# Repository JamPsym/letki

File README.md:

# Letki modular LED display

Letki is a low-cost chain of 8×8 LED tiles with PWM brightness, programmable
text/graphics and synchronized music shows. The current physical baseline is
five v3 boards running the UART-programmable **general firmware R3**. The
independently developed v3.2 hardware and ESP8266/X035 attachment are the next
workstreams; their preparation and qualification status are recorded separately.

## Start here

- [Documentation index](docs/README.md): architecture, firmware, hardware and tests.
- [Current project state](docs/current-state.md): accepted revisions, orders,
  assembly substitutions and next work; later dated entries supersede older ones.
- [R3 milestone](docs/milestones/v3-general-r3-20261017.txt): verified five-board
  firmware, recovery references and physical validation limits.
- [Contributor instructions](AGENTS.md): working rules and hardware permissions.
- [Toolchain setup](docs/arch-setup.md): compiler and host dependencies.

## Desktop app and music

[Letki Studio](host/control/README.md) is a native GTK4/libadwaita application.
It provides text/font controls, brightness modulation, a five-tile pixel canvas,
presets, diagnostics and demos. The `letkid` service owns UART; Studio, the CLI
and other applications share its [local API](host/control/API.md).

```sh
make control-run
```

Drafts stay local until Apply. Applied RAM content runs independently of the GUI;
power cycling restores the saved flash show. Content uploads do not reflash the
application. Close picocom before connecting the service.

The [native C++ player](host/player/README.txt) uses the audio playback clock for
video and LED timing. Studio's Demo tab lists all [five music/video shows](docs/music-demos.md),
including the Laskowski × 2Pac mashup. Video plays on the PC beside the simulator.

```sh
make player
build/player/letki-player --show config/player/my-cyganie-full.json --simulate
make demos-prepare
```

`--simulate` forces PC-only playback. The direct player otherwise discovers a
WCH-Link UART adapter; release the broker's UART connection before using it.
`make demos-prepare` validates and renders local media offline without opening
UART or playing audio. Recordings are optional local data, not included in Git.

## Firmware and checks

The default build retains the original single-board text v3 application. Build
the current five-board general firmware with `make general-images`.

```sh
make doctor
make -j4
make general-images -j4
make test
make all-variants -j4
make player-test
make control-test
```

Builds never program a board. Physical tests and firmware writes follow the
identification, backup, readback and permission rules in [AGENTS.md](AGENTS.md).
Host register mocks and simulations do not establish electrical qualification.

## Layout

| Directory | Contents |
| --- | --- |
| `firmware/` | Maintained applications and separate diagnostic/demo variants |
| `host/` | Native Studio/service, music player and firmware renderers |
| `hw/` | Active KiCad projects, local libraries and mechanical sources |
| `config/` | Project settings, show cue sheets and selected purchase records |
| `scripts/` | Build/setup helpers, host controls and scoped CAD tools |
| `tests/` | Firmware register mocks and host/integration checks |
| `docs/` | Current decisions, architecture, validation and dated history |
| `archive/` | Superseded firmware, hardware and purchase drafts |
| `build/` | Ignored binaries, raw test evidence, media and working experiments |

See [hardware projects](hw/README.md) before opening a board. Existing v3 boards
require the documented C1–C3 ground repair. CAD and manufacturing exports have
their own qualification status; a successful software build is not a fabrication
release. Historical variants retain their notices and remain buildable.

## Development context and local data

The [attachment architecture](docs/attachments-study-20261017.txt) keeps tile
protocols independent of the host: ESP8266 → SPI → X035 → display. The media/TV
host is the **last planned system component**, with the spare N5095/M2S as a
candidate; development can continue after its integration.

Project decisions and source belong in Git. Generated binaries, recordings,
readbacks, caches, CAD editor state and fabrication exports remain local.
Shared electronics inventory is maintained outside this repository; see
[configuration setup](config/README.md) before using procurement generators.
These local datasets and raw evidence need their own backup.

The earlier root README is preserved in [development history](docs/development-history.md).

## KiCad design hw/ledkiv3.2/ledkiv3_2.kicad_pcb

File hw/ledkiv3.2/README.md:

# Letki v3.2 — checked five-board prototype candidate

Open `ledkiv3_2.kicad_pro`. CH32V006E8R6/QSOP24, 49.6 mm square, 6.2 mm pixels;
west-to-east USART1, south-to-north USART2, shared I²C and separate LED blanking.
All 159 original component placements and padstacks are preserved.

The accepted main milestone is preserved unchanged. This fabrication derivative
removes its dangling `/ADDR0` stub, restores the Q3/R25 supply branch widths
and selects six exact passive MPNs. It has 1,489 segments and 299 fixed vias.
The two J2 pin1-marker silk lines also have improved pad clearance.
Fresh ERC, DRC, opens, parity and ignored findings are all zero; independent
continuity confirms all 76 nets. All 159 placements and padstacks remain fixed.
[Fabrication identity](fabrication.json) records the exact source and scope.
Power uses In2 VCC plus stitched front reinforcement; In1 has seven explicitly
reviewed signal segments on two nets. See [routing and limits](ROUTING.txt).

The full unrouted checkpoint for human routing is
`../../archive/hw/ledkiv3.2-unrouted-20261017/` from the repository root;
copy its complete folder before editing. v3.1 remains preserved.

Current checked exports belong in `exports/fabrication-20261017-r2/`. The older
`exports/prototype/` is historical. Read [the handoff](../../docs/v3_2-fabrication-20261017.txt)
and [assembly instructions](ASSEMBLY.txt). This is CAD for a prototype;
physical electrical/mechanical qualification remains. JLCONE defaults are
user-selected for the prototype; currentr2Gerbers are uploaded and the
reference preview inspected. Final engineering production files are unconfirmed.
The existing v3/v3.1 firmware is incompatible; the new application and custom
loader have not been implemented or flashed. The older diffuser does not fit.
No stock reservation or purchase is implied.

The user subsequently confirmed ordering **15 bare boards, split 5+10**, on
17 October 2026. See [the order and next steps](../../docs/v3_2-order-and-bringup.txt).
Receipt is pending; the paid amount and supplier order number are unverified.
The checked export retains its original five-board assembly snapshot. The
[new requirements worksheet](../../config/purchase/v3_2-assembly-requirements-20261017.csv)
covers fifteen v3.2 plus the separate five v3.1 boards, without changing stock
or this CAD. Incoming AliExpress parts are recorded in Electronics; firmware
and physical component/tile qualification remain pending.

## Accepted milestone and manual editing

The parent accepted main milestone is `v3_2-main-20261017`, preserved in
`archive/hw/ledkiv3.2-main-milestone-20261017/` from the repository root.
[Acceptance record](baseline.json) binds the frozen accepted milestone and its
checks; `fabrication.json` binds the current derivative.
The first robot-routed milestone `v3_2-routed-20261017` remains frozen in
`archive/hw/ledkiv3.2-routed-milestone-20261017/` for comparison.

**Continue manual component/placement/routing changes in this main project.**
The milestones and older unrouted checkpoint stay frozen. The new fabrication export identifies this derivative. Historical exports and
comparison snapshots retain their original source identities. Changed CAD needs
fresh checks and deliberate review of baseline-specific contracts. Preserve later human edits.

## Historical trace cleanup of the manual working state (2026-10-17)

The one-chain cleanup retained 68 checked, visually reviewed replacements:
1,850 track segments became 1,594. All 299 vias, 159 footprints, native padstacks,
net topology, widths, supply routing and inner-layer copper are preserved.
All 76 nets remain independently connected; native unconnected items and
schematic parity are zero. The pre-existing dangling `/ADDR0` track warning
remains; no new native findings were introduced. Nineteen proposals made no
useful change; four proposals had ambiguous external contacts and one did not
reduce actual bends, so those five were rejected.

Use the [trace cleanup workflow](../../docs/v3_2-trace-cleanup.txt) for another
isolated pass or one selected chain. Before/after renders, per-chain checks,
source backup and application hashes are in
`build/hardware/v3_2-trace-cleanup-checked-20261017/` from the repository root.
The accepted routed milestone stays frozen. Existing exports describe their
recorded earlier source and need regeneration before fabrication use.

## Historical point-to-point routing follow-up (2026-10-17)

An additional 50 complete connections were deleted and freshly routed with A*,
one at a time, with copper pours excluded from the search: 48 on F.Cu and two
on B.Cu. The main board now has 1,490 track segments, down from 1,594. The
affected paths have 97 fewer bends and add 5.693 mm total length; each accepted
increase stays within both 5% and 0.25 mm. All vias, placements, widths, net
junctions, power routing and inner-layer tracks remain fixed. Thirty-three
unhelpful or rejected proposals retained their original copper.

Native DRC/parity findings remain identical to the manual-state baseline,
including the existing `/ADDR0` dangling-track warning. All 76 nets remain
independently connected after zone refill. Evidence, native comparison renders,
the exact previous PCB and application hashes are in
`build/hardware/v3_2-point-reroute-checked-20261017/` from the repository root.
The source schematic/project/rules and frozen milestone are preserved; existing
fabrication exports still describe their earlier source.

The [first robot version / current routing comparison](https://psym.pl/zobaczadas/v3.2-comparison/)
shows all four layers with linked net highlighting, zoom/pan and a wipe view.
It compares the frozen 2,015-segment milestone with the current 1,490-segment
board, including the manual changes before cleanup. Website source is under
`~/local_network/pieslab0/websites/psym.pl/zobaczadas/`; SVG provenance and
browser/deployment checks are in `build/hardware/v3_2-web-comparison-20261017/`.

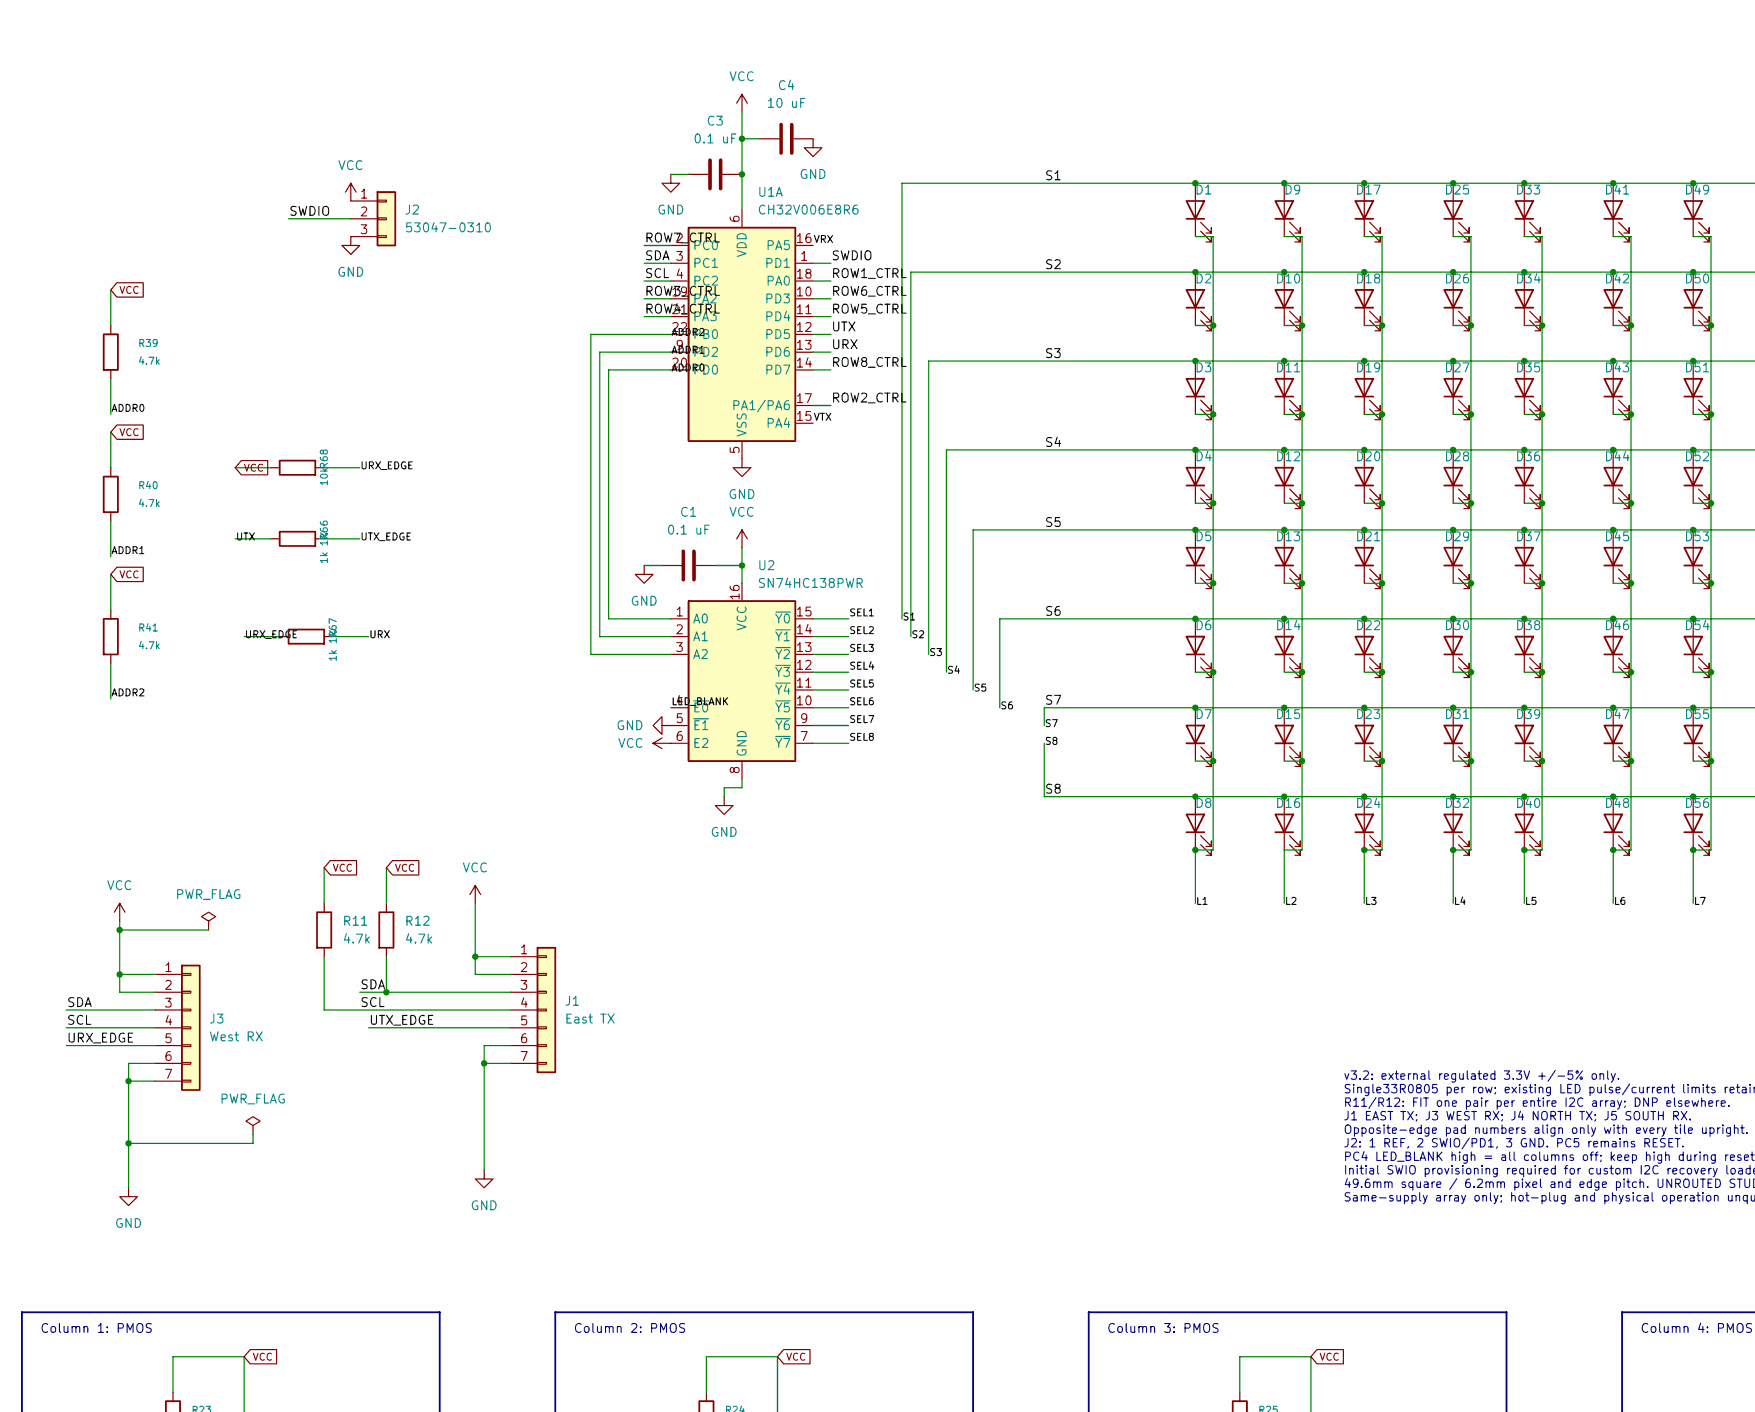
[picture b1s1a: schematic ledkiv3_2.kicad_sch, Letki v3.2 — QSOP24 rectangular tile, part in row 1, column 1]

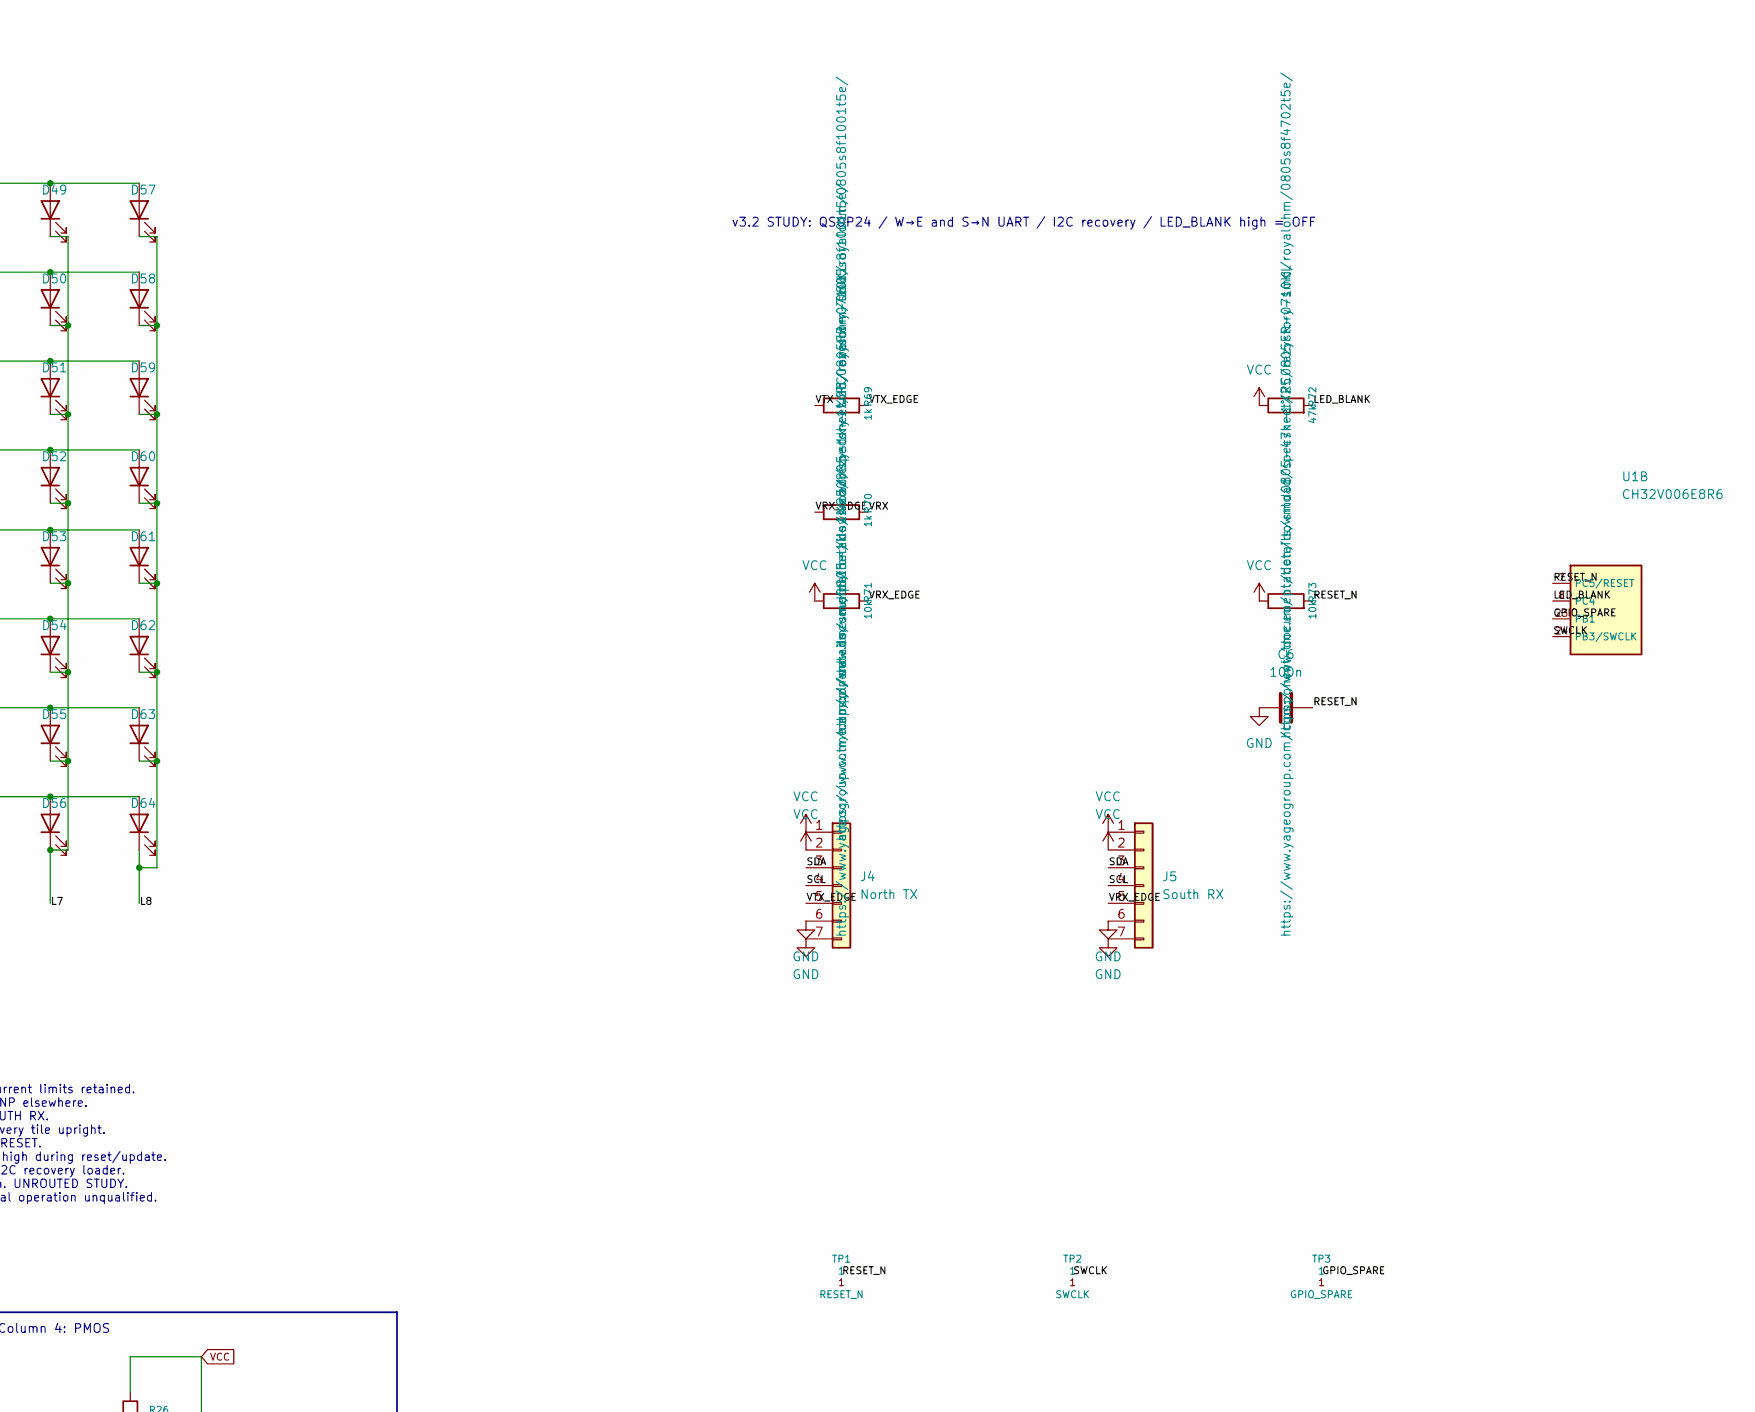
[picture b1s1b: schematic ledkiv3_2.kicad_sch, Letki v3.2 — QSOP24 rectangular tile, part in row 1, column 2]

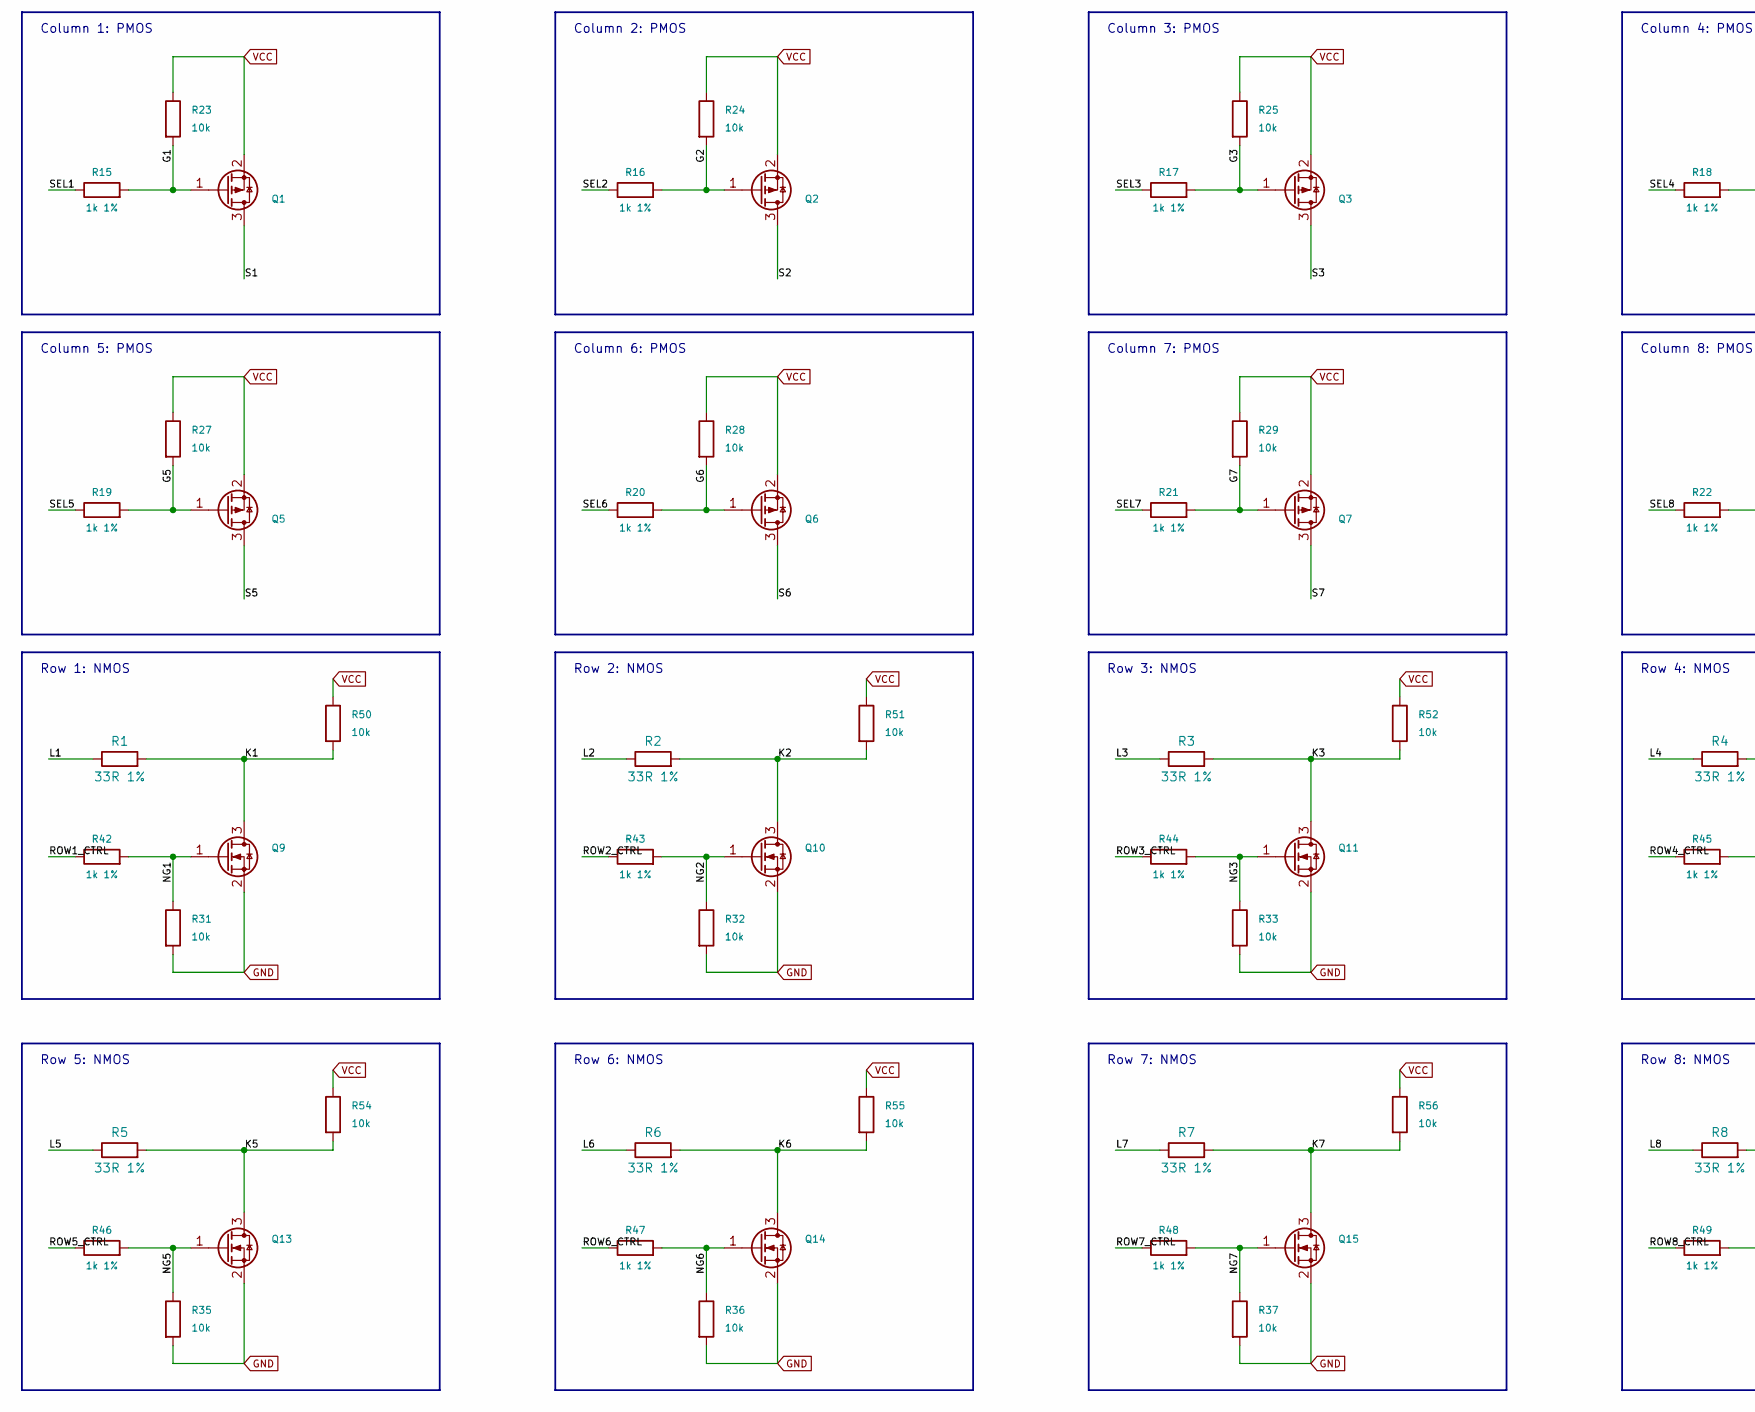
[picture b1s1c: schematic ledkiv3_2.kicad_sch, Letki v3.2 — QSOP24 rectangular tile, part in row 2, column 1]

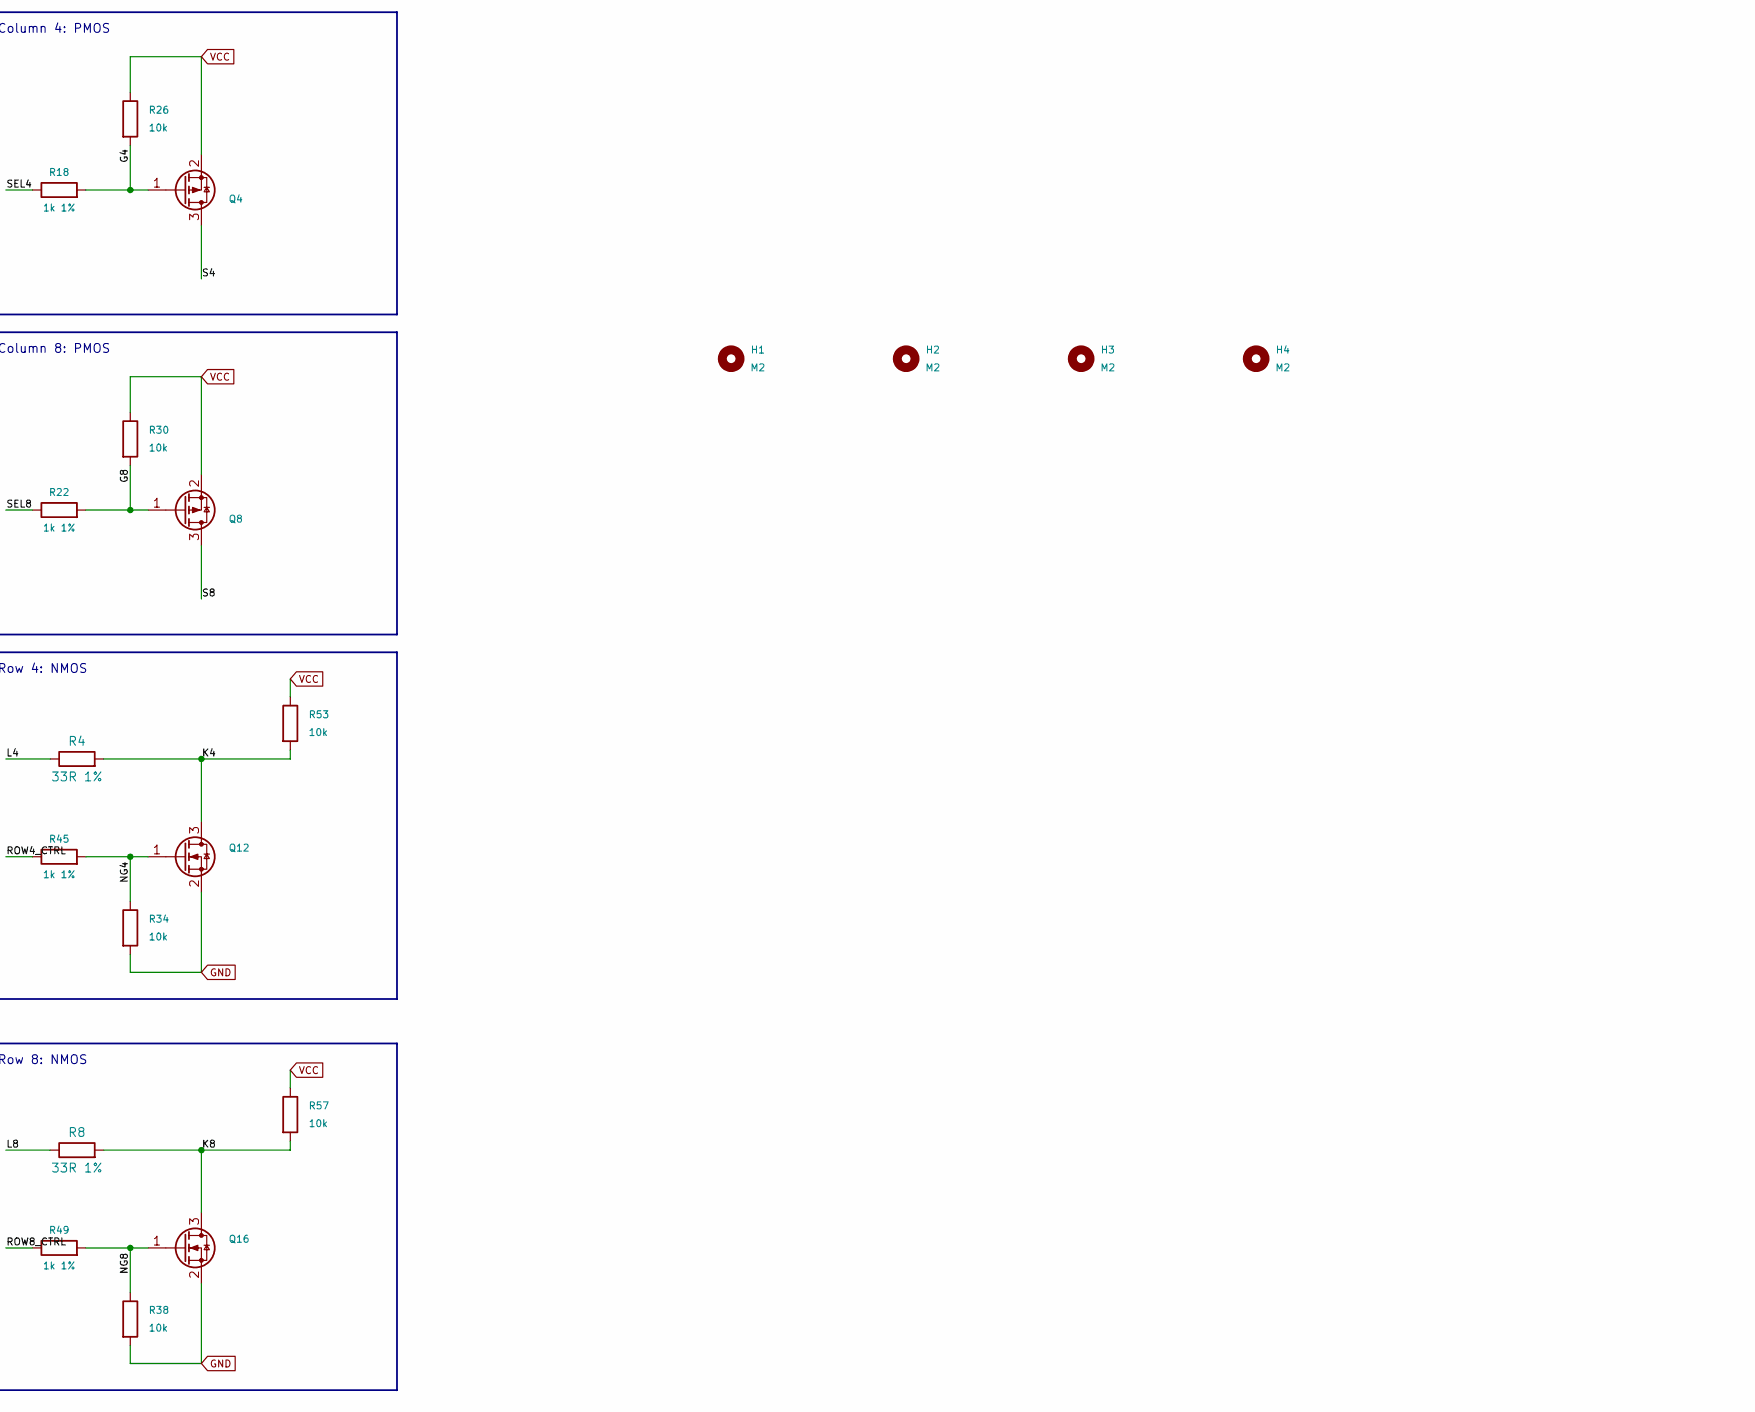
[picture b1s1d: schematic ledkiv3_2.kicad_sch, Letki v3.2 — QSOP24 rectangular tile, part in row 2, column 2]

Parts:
C1, C3: 0.1 uF; C_0805_2012Metric_Pad1.18x1.45mm_HandSolder; MPN C0805B104K500NT
C4: 10 uF; C_0805_2012Metric_Pad1.18x1.45mm_HandSolder; MPN CL21A106KAYNNNE
C6: 100n; C_0805_2012Metric_Pad1.18x1.45mm_HandSolder; MPN C0805B104K500NT
D1, D2, D3, D4, D5, D6, D7, D8, D9, D10, D11, D12, D13, D14, D15, D16, D17, D18, D19, D20, D21, D22, D23, D24, D25, D26, D27, D28, D29, D30, D31, D32, D33, D34, D35, D36, D37, D38, D39, D40, D41, D42, D43, D44, D45, D46, D47, D48, D49, D50, D51, D52, D53, D54, D55, D56, D57, D58, D59, D60, D61, D62, D63, D64: XL-2012UOC; LED_0805_2012Metric_LetkiFab; MPN XL-2012UOC
H1, H2, H3, H4: M2; MountingHole_2.2mm_M2_LetkiFab
J1: East TX; EdgeWire_1x07_P6.2mm_D0.8mm
J2: 53047-0310; Molex_PicoBlade_53047-0310_1x03_P1.25mm_Vertical_SWIO_Letki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; MPN 530470310
J3: West RX; EdgeWire_1x07_P6.2mm_D0.8mm
J4: North TX; EdgeWire_1x07_P6.2mm_D0.8mm
J5: South RX; EdgeWire_1x07_P6.2mm_D0.8mm
Q1, Q2, Q3, Q4, Q5, Q6, Q7, Q8: AO3415A; SOT-23; MPN AO3415A
Q9, Q10, Q11, Q12, Q13, Q14, Q15, Q16: DMN2056U-7; SOT-23; MPN DMN2056U-7
R1, R2, R3, R4, R5, R6, R7, R8: 33R 1%; R_0805_2012Metric_Pad1.20x1.40mm_HandSolder; MPN 0805S8F330JT5E
R11, R12, R39, R40, R41: 4.7k; R_0805_2012Metric_Pad1.20x1.40mm_HandSolder; MPN 0805W8J0472T5E
R15, R16, R17, R18, R19, R20, R21, R22, R42, R43, R44, R45, R46, R47, R48, R49: 1k 1%; R_0603_1608Metric_Pad0.98x0.95mm_HandSolder; MPN 0603SAF1001T5E
R23, R24, R25, R26, R27, R28, R29, R30, R31, R32, R33, R34, R35, R36, R37, R38, R50, R51, R52, R53, R54, R55, R56, R57: 10k; R_0603_1608Metric_Pad0.98x0.95mm_HandSolder; MPN 0603SAF1002T5E
R66, R67: 1k 1%; R_0805_2012Metric_Pad1.20x1.40mm_HandSolder; MPN 0805S8F1001T5E
R68, R71, R73: 10k; R_0805_2012Metric_Pad1.20x1.40mm_HandSolder; MPN RC0805FR-0710KL
R69, R70: 1k; R_0805_2012Metric_Pad1.20x1.40mm_HandSolder; MPN 0805S8F1001T5E
R72: 47k; R_0805_2012Metric_Pad1.20x1.40mm_HandSolder; MPN 0805S8F4702T5E
TP1: RESET_N; TestPoint_1.5mm
TP2: SWCLK; TestPoint_1.5mm
TP3: GPIO_SPARE; TestPoint_1.5mm
U1: CH32V006E8R6; QSOP-24_3.9x8.7mm_P0.635mm; MPN CH32V006E8R6
U2: SN74HC138PWR; TSSOP-16_4.4x5mm_P0.65mm; MPN SN74HC138PWR

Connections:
/ADDR0: R39.2, U1.20 (PD0), U2.1 (A0)
/ADDR1: R40.2, U1.9 (PD2), U2.2 (A1)
/ADDR2: R41.2, U1.22 (PB0), U2.3 (A2)
/G1: Q1.1 (G), R15.2, R23.2
/G2: Q2.1 (G), R16.2, R24.2
/G3: Q3.1 (G), R17.2, R25.2
/G4: Q4.1 (G), R18.2, R26.2
/G5: Q5.1 (G), R19.2, R27.2
/G6: Q6.1 (G), R20.2, R28.2
/G7: Q7.1 (G), R21.2, R29.2
/G8: Q8.1 (G), R22.2, R30.2
/GPIO_SPARE: TP3.1, U1.23 (PB1)
/K1: Q9.3 (D), R1.2, R50.2
/K2: Q10.3 (D), R2.2, R51.2
/K3: Q11.3 (D), R3.2, R52.2
/K4: Q12.3 (D), R4.2, R53.2
/K5: Q13.3 (D), R5.2, R54.2
/K6: Q14.3 (D), R6.2, R55.2
/K7: Q15.3 (D), R7.2, R56.2
/K8: Q16.3 (D), R8.2, R57.2
/L1: D1.1 (K), D2.1 (K), D3.1 (K), D4.1 (K), D5.1 (K), D6.1 (K), D7.1 (K), D8.1 (K), R1.1
/L2: D9.1 (K), D10.1 (K), D11.1 (K), D12.1 (K), D13.1 (K), D14.1 (K), D15.1 (K), D16.1 (K), R2.1
/L3: D17.1 (K), D18.1 (K), D19.1 (K), D20.1 (K), D21.1 (K), D22.1 (K), D23.1 (K), D24.1 (K), R3.1
/L4: D25.1 (K), D26.1 (K), D27.1 (K), D28.1 (K), D29.1 (K), D30.1 (K), D31.1 (K), D32.1 (K), R4.1
/L5: D33.1 (K), D34.1 (K), D35.1 (K), D36.1 (K), D37.1 (K), D38.1 (K), D39.1 (K), D40.1 (K), R5.1
/L6: D41.1 (K), D42.1 (K), D43.1 (K), D44.1 (K), D45.1 (K), D46.1 (K), D47.1 (K), D48.1 (K), R6.1
/L7: D49.1 (K), D50.1 (K), D51.1 (K), D52.1 (K), D53.1 (K), D54.1 (K), D55.1 (K), D56.1 (K), R7.1
/L8: D57.1 (K), D58.1 (K), D59.1 (K), D60.1 (K), D61.1 (K), D62.1 (K), D63.1 (K), D64.1 (K), R8.1
/LED_BLANK: R72.2, U1.8 (PC4), U2.4 (~E0)
/NG1: Q9.1 (G), R31.1, R42.2
/NG2: Q10.1 (G), R32.1, R43.2
/NG3: Q11.1 (G), R33.1, R44.2
/NG4: Q12.1 (G), R34.1, R45.2
/NG5: Q13.1 (G), R35.1, R46.2
/NG6: Q14.1 (G), R36.1, R47.2
/NG7: Q15.1 (G), R37.1, R48.2
/NG8: Q16.1 (G), R38.1, R49.2
/RESET_N: C6.2, R73.2, TP1.1, U1.7 (PC5/RESET)
/ROW1_CTRL: R42.1, U1.18 (PA0)
/ROW2_CTRL: R43.1, U1.17 (PA1/PA6)
/ROW3_CTRL: R44.1, U1.19 (PA2)
/ROW4_CTRL: R45.1, U1.21 (PA3)
/ROW5_CTRL: R46.1, U1.11 (PD4)
/ROW6_CTRL: R47.1, U1.10 (PD3)
/ROW7_CTRL: R48.1, U1.2 (PC0)
/ROW8_CTRL: R49.1, U1.14 (PD7)
/S1: D1.2 (A), D9.2 (A), D17.2 (A), D25.2 (A), D33.2 (A), D41.2 (A), D49.2 (A), D57.2 (A), Q1.3 (D)
/S2: D2.2 (A), D10.2 (A), D18.2 (A), D26.2 (A), D34.2 (A), D42.2 (A), D50.2 (A), D58.2 (A), Q2.3 (D)
/S3: D3.2 (A), D11.2 (A), D19.2 (A), D27.2 (A), D35.2 (A), D43.2 (A), D51.2 (A), D59.2 (A), Q3.3 (D)
/S4: D4.2 (A), D12.2 (A), D20.2 (A), D28.2 (A), D36.2 (A), D44.2 (A), D52.2 (A), D60.2 (A), Q4.3 (D)
/S5: D5.2 (A), D13.2 (A), D21.2 (A), D29.2 (A), D37.2 (A), D45.2 (A), D53.2 (A), D61.2 (A), Q5.3 (D)
/S6: D6.2 (A), D14.2 (A), D22.2 (A), D30.2 (A), D38.2 (A), D46.2 (A), D54.2 (A), D62.2 (A), Q6.3 (D)
/S7: D7.2 (A), D15.2 (A), D23.2 (A), D31.2 (A), D39.2 (A), D47.2 (A), D55.2 (A), D63.2 (A), Q7.3 (D)
/S8: D8.2 (A), D16.2 (A), D24.2 (A), D32.2 (A), D40.2 (A), D48.2 (A), D56.2 (A), D64.2 (A), Q8.3 (D)
/SCL: J1.4, J3.4, J4.4, J5.4, R11.2, U1.4 (PC2)
/SDA: J1.3, J3.3, J4.3, J5.3, R12.2, U1.3 (PC1)
/SEL1: R15.1, U2.15 (~Y0)
/SEL2: R16.1, U2.14 (~Y1)
/SEL3: R17.1, U2.13 (~Y2)
/SEL4: R18.1, U2.12 (~Y3)
/SEL5: R19.1, U2.11 (~Y4)
/SEL6: R20.1, U2.10 (~Y5)
/SEL7: R21.1, U2.9 (~Y6)
/SEL8: R22.1, U2.7 (~Y7)
/SWCLK: TP2.1, U1.24 (PB3/SWCLK)
/SWDIO: J2.2, U1.1 (PD1)
/URX: R67.2, U1.13 (PD6)
/URX_EDGE: J3.5, R67.1, R68.2
/UTX: R66.1, U1.12 (PD5)
/UTX_EDGE: J1.5, R66.2
/VRX: R70.2, U1.16 (PA5)
/VRX_EDGE: J5.5, R70.1, R71.2
/VTX: R69.1, U1.15 (PA4)
/VTX_EDGE: J4.5, R69.2
GND: C1.1, C3.1, C4.2, C6.1, J1.6, J1.7, J2.3, J3.6, J3.7, J4.6, J4.7, J5.6, J5.7, Q9.2 (S), Q10.2 (S), Q11.2 (S), Q12.2 (S), Q13.2 (S), Q14.2 (S), Q15.2 (S), Q16.2 (S), R31.2, R32.2, R33.2, R34.2, R35.2, R36.2, R37.2, R38.2, U1.5 (VSS), U2.5 (~E1), U2.8 (GND)
VCC: C1.2, C3.2, C4.1, J1.1, J1.2, J2.1, J3.1, J3.2, J4.1, J4.2, J5.1, J5.2, Q1.2 (S), Q2.2 (S), Q3.2 (S), Q4.2 (S), Q5.2 (S), Q6.2 (S), Q7.2 (S), Q8.2 (S), R11.1, R12.1, R23.1, R24.1, R25.1, R26.1, R27.1, R28.1, R29.1, R30.1, R39.1, R40.1, R41.1, R50.1, R51.1, R52.1, R53.1, R54.1, R55.1, R56.1, R57.1, R68.1, R71.1, R72.1, R73.1, U1.6 (VDD), U2.6 (E2), U2.16 (VCC)

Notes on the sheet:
v3.2: external regulated 3.3V +/-5% only. Single33R0805 per row; existing LED pulse/current limits retained. R11/R12: FIT one pair per entire I2C array; DNP elsewhere. J1 EAST TX; J3 WEST RX; J4 NORTH TX; J5 SOUTH RX. Opposite-edge pad numbers align only with every tile upright. J2: 1 REF, 2 SWIO/P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
Column 8: PMOS
Column 6: PMOS
Column 4: PMOS
Column 2: PMOS
Row 6: NMOS
Row 2: NMOS
Column 7: PMOS
Row 5: NMOS
Row 7: NMOS
Row 1: NMOS
Column 5: PMOS
Column 3: PMOS
Row 8: NMOS
Row 4: NMOS
Column 1: PMOS
Row 3: NMOS
v3.2 STUDY: QSOP24 / W→E and S→N UART / I2C recovery / LED_BLANK high = OFF

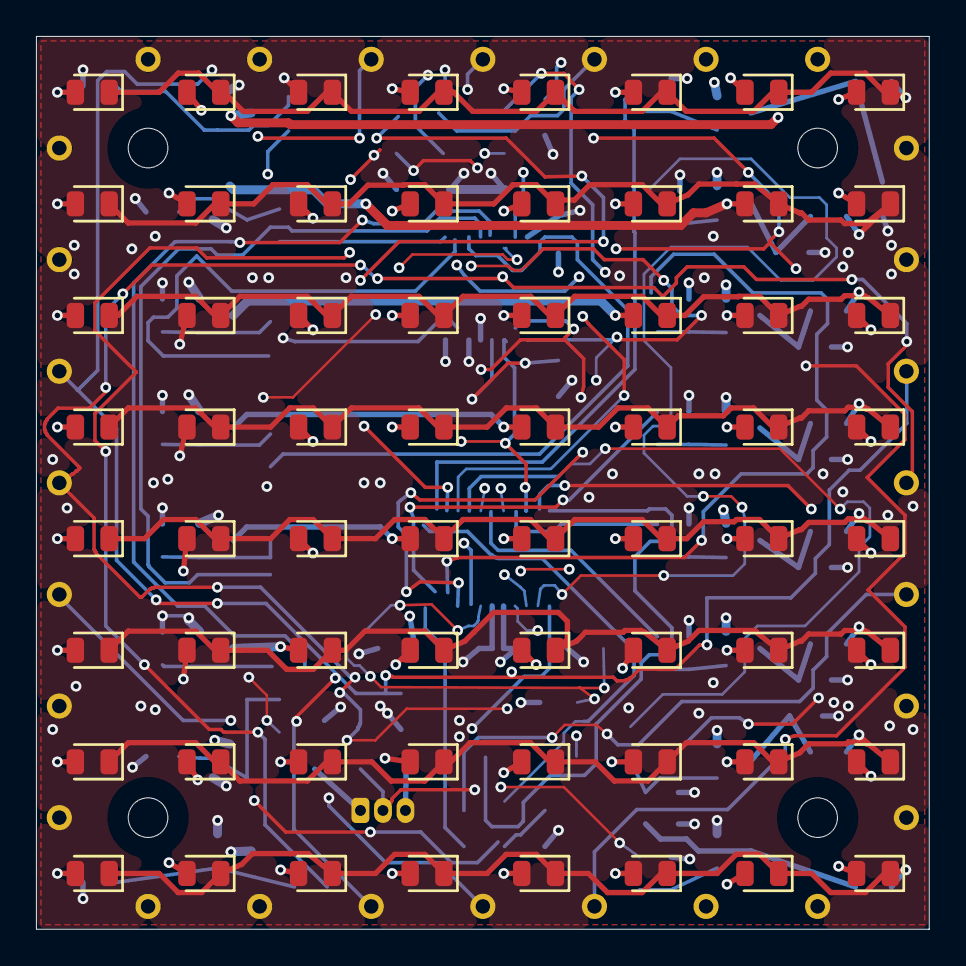
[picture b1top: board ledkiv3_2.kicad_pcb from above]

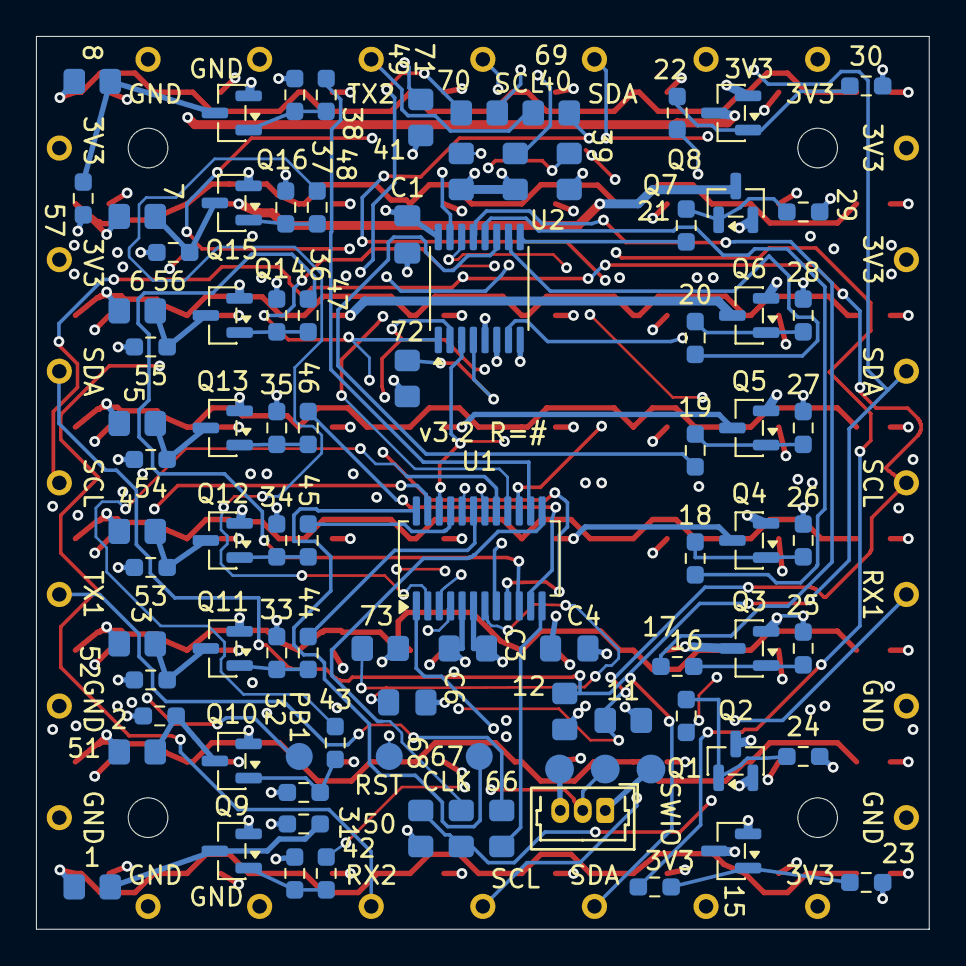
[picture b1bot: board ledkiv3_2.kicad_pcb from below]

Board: 4 copper layers, 49.6 x 49.6 mm, 159 parts (91 on the bottom side), 76 nets.
